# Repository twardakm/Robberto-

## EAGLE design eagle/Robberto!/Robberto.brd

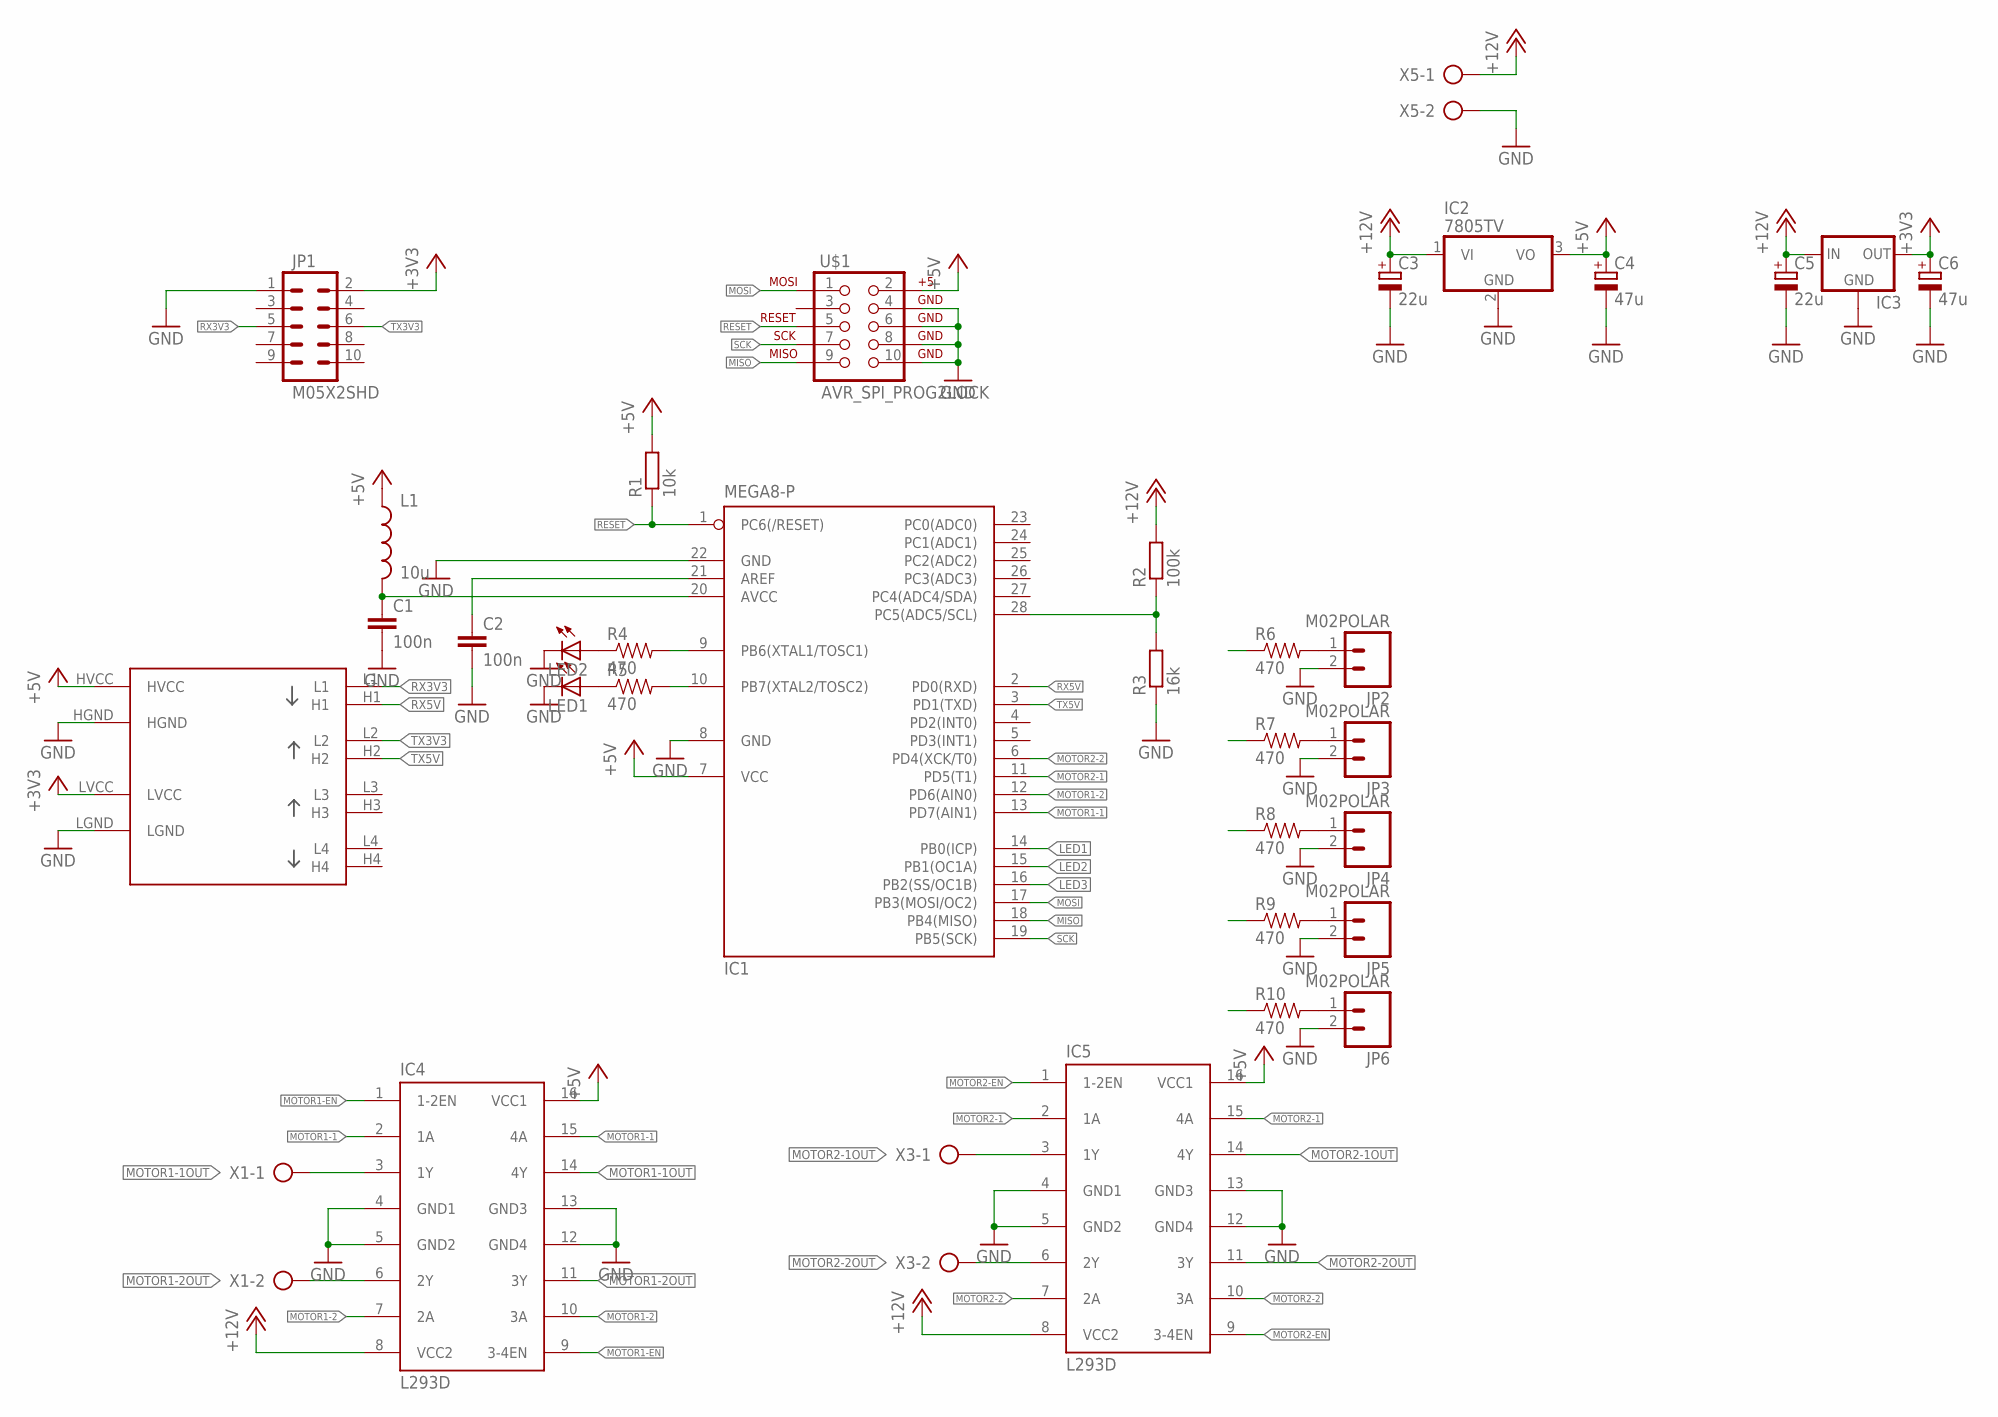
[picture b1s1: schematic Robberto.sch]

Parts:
C1, C2: 100n; C0805
C3, C5: 22u; E2,5-7
C4, C6: 47u; E2,5-7
IC1: MEGA8-P; DIL28-3
IC2: 7805TV; TO220V
IC3: LFXXCVS; TO220S
IC4, IC5: L293D; DIL16
JP1: M05X2SHD; 2X5-SHROUDED
JP2, JP3, JP4, JP5, JP6: M02POLAR; MOLEX-1X2
L1: 10u; 0805
LED1, LED2: LEDSML0805; SML0805
R1: 10k; M0805
R2: 100k; M0805
R3: 16k; M0805
R4, R5, R6, R7, R8, R9, R10: 470; 0805
U$1: AVR_SPI_PROG2LOCK; 2X5-SHROUDED_LOCK
U$2: ELECTROPARK
X1, X3, X5: AK300/2

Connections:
+3V3: C6.+, IC3.3 (OUT), JP1.2, U$2.LVCC
+5V: C4.+, IC1.7 (VCC), IC2.3 (VO), IC4.16 (VCC1), IC5.16 (VCC1), L1.1, R1.2, U$1.2, U$2.HVCC
+12V: C3.+, C5.+, IC2.1 (VI), IC3.1 (IN), IC4.8 (VCC2), IC5.8 (VCC2), R2.2, X5.1
GND: C1.2, C2.2, C3.-, C4.-, C5.-, C6.-, IC1.8 (GND), IC1.22 (GND), IC2.2 (GND), IC3.2 (GND), IC4.4 (GND1), IC4.5 (GND2), IC4.12 (GND4), IC4.13 (GND3), IC5.4 (GND1), IC5.5 (GND2), IC5.12 (GND4), IC5.13 (GND3), JP1.1, JP2.2, JP3.2, JP4.2, JP5.2, JP6.2, LED1.C, LED2.C, R3.1, U$1.4, U$1.6, U$1.8, U$1.10, U$2.HGND, U$2.LGND, X5.2
LED1: IC1.14 (PB0(ICP)), R6.1
LED2: IC1.15 (PB1(OC1A)), R7.1
LED3: IC1.16 (PB2(SS/OC1B)), R8.1
MISO: IC1.18 (PB4(MISO)), R10.1, U$1.9
MOSI: IC1.17 (PB3(MOSI/OC2)), R9.1, U$1.1
MOTOR1-1: IC1.13 (PD7(AIN1)), IC4.2 (1A), IC4.15 (4A)
MOTOR1-1OUT: IC4.3 (1Y), IC4.14 (4Y), X1.1
MOTOR1-2: IC1.12 (PD6(AIN0)), IC4.7 (2A), IC4.10 (3A)
MOTOR1-2OUT: IC4.6 (2Y), IC4.11 (3Y), X1.2
MOTOR1-EN: IC4.1 (1-2EN), IC4.9 (3-4EN)
MOTOR2-1: IC1.11 (PD5(T1)), IC5.2 (1A), IC5.15 (4A)
MOTOR2-1OUT: IC5.3 (1Y), IC5.14 (4Y), X3.1
MOTOR2-2: IC1.6 (PD4(XCK/T0)), IC5.7 (2A), IC5.10 (3A)
MOTOR2-2OUT: IC5.6 (2Y), IC5.11 (3Y), X3.2
MOTOR2-EN: IC5.1 (1-2EN), IC5.9 (3-4EN)
unnamed: C1.1, IC1.20 (AVCC), L1.2
unnamed: C2.1, IC1.21 (AREF)
unnamed: IC1.28 (PC5(ADC5/SCL)), R2.1, R3.2
unnamed: LED2.A, R4.1
unnamed: LED1.A, R5.1
unnamed: IC1.10 (PB7(XTAL2/TOSC2)), R5.2
unnamed: IC1.9 (PB6(XTAL1/TOSC1)), R4.2
unnamed: JP2.1, R6.2
unnamed: JP3.1, R7.2
unnamed: JP4.1, R8.2
unnamed: JP5.1, R9.2
unnamed: JP6.1, R10.2
RESET: IC1.1 (PC6(/RESET)), R1.1, U$1.5
RX3V3: JP1.5, U$2.L1
RX5V: IC1.2 (PD0(RXD)), U$2.H1
SCK: IC1.19 (PB5(SCK)), U$1.7
TX3V3: JP1.6, U$2.L2
TX5V: IC1.3 (PD1(TXD)), U$2.H2

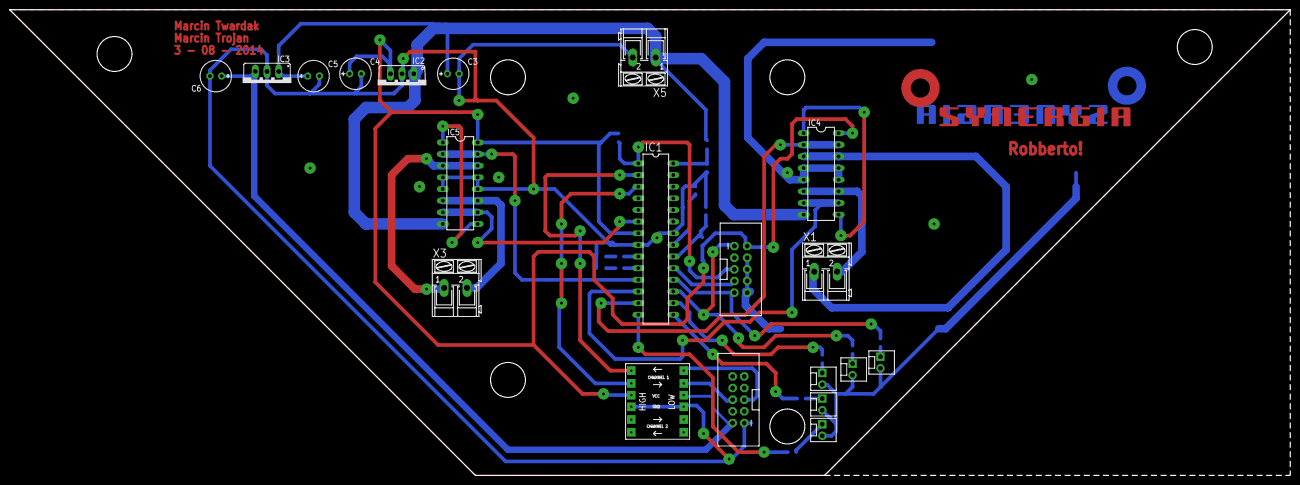
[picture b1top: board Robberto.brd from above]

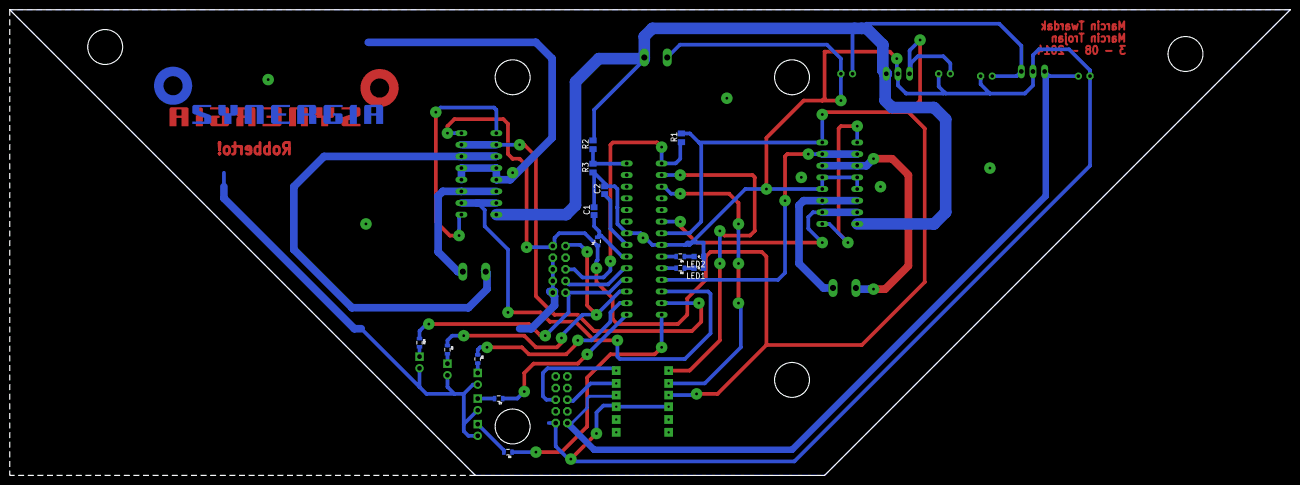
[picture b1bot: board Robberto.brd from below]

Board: 2 copper layers, 279.4 x 101.6 mm, 37 parts (16 on the bottom side), 37 nets.

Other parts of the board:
U$3, U$4: SYNERGIA_50MM

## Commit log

2014-09-05 Bluetooth is working
2014-09-05 fast coded. WSAD is working but wrong (needed continuous clicking)
2014-09-05 LabVIEW improved + eagle files
2014-09-06 Steering with arrows works fine!

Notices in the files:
parts and their libraries:
SparkFun-Connectors: Licensing: Creative Commons ShareAlike 4.0 International - https://creativecommons.org/licenses/by-sa/4.0
